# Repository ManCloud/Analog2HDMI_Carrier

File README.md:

# Analog2HDMI_Carrier
A breakout/carrier board for the Analog2HMDI adapter by Electron Shepherd LLC

Original project of the Circuit-Board.de / The-New-Retro (Discord) Community.

## Case
 https://www.printables.com/de/model/156339-analog2hdmi-case-for-manclouds-pcb
 
 ## Powered by:
 - jotheripper https://twitter.com/jotheripper_ (case)
 - FuNzeL https://twitter.com/Funzel86 (organization / ideas)
 - BambooShadow https://twitter.com/BambooShadow (prototyping)
 - derKevin https://twitter.com/kinoX_51 (ideas)
 - and the ones i forgot to mention.

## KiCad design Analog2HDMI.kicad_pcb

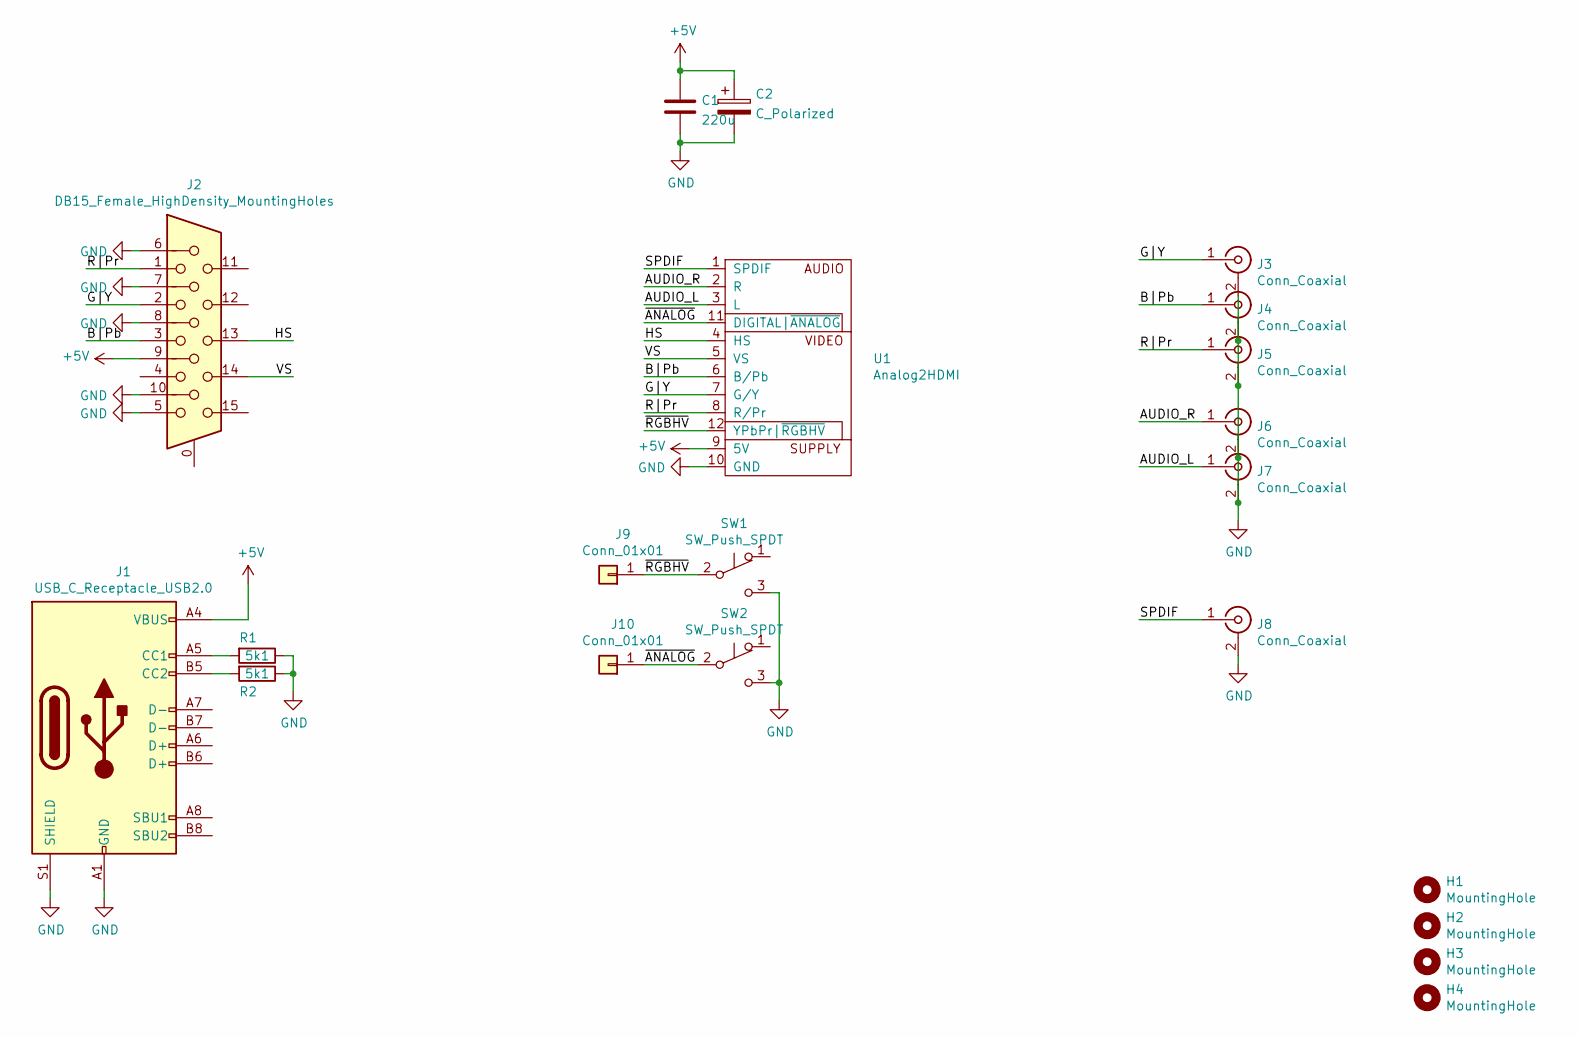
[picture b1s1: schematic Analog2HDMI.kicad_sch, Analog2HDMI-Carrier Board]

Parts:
C1: 220u; C_1206_3216Metric_Pad1.33x1.80mm_HandSolder
C2: C_Polarized; CP_Elec_6.3x7.7
H1, H2, H3, H4: MountingHole; MountingHole_2.1mm
J1: USB_C_Receptacle_USB2.0; USB_C_Receptacle_HRO_TYPE-C-31-M-12
J2: DB15_Female_HighDensity_MountingHoles; DSUB-15-HD_Female_Horizontal_P2.29x1.98mm_EdgePinOffset3.03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
J3, J4, J5, J6, J7, J8: Conn_Coaxial; AV-8.4-9
J9, J10: Conn_01x01; TestPoint_Pad_1.5x1.5mm
R1, R2: 5k1; R_1206_3216Metric
SW1, SW2: SW_Push_SPDT; SW_CuK_OS102011MA1QN1_SPDT_Angled
U1: Analog2HDMI

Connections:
+5V: C1.1, C2.1, J1.A4 (VBUS), J1.A9 (VBUS), J1.B4 (VBUS), J1.B9 (VBUS), J2.9, U1.9 (5V)
/AUDIO_L: J7.1 (In), U1.3 (L)
/AUDIO_R: J6.1 (In), U1.2 (R)
/B|Pb: J2.3, J4.1 (In), U1.6 (B/Pb)
/G|Y: J2.2, J3.1 (In), U1.7 (G/Y)
/HS: J2.13, U1.4 (HS)
/R|Pr: J2.1, J5.1 (In), U1.8 (R/Pr)
/SPDIF: J8.1 (In), U1.1 (SPDIF)
/VS: J2.14, U1.5 (VS)
/~ANALOG: J10.1, SW2.2 (B), U1.11 (DIGITAL|~ANALOG)
/~RGBHV: J9.1, SW1.2 (B), U1.12 (YPbPr|~RGBHV)
GND: C1.2, C2.2, J1.A1 (GND), J1.A12 (GND), J1.B1 (GND), J1.B12 (GND), J1.S1 (SHIELD), J2.5, J2.6, J2.7, J2.8, J2.10, J3.2 (Ext), J4.2 (Ext), J5.2 (Ext), J6.2 (Ext), J7.2 (Ext), J8.2 (Ext), R1.1, R2.1, SW1.3 (C), SW2.3 (C), U1.10 (GND)
unnamed: J1.A5 (CC1), R1.2
unnamed: J1.B5 (CC2), R2.2

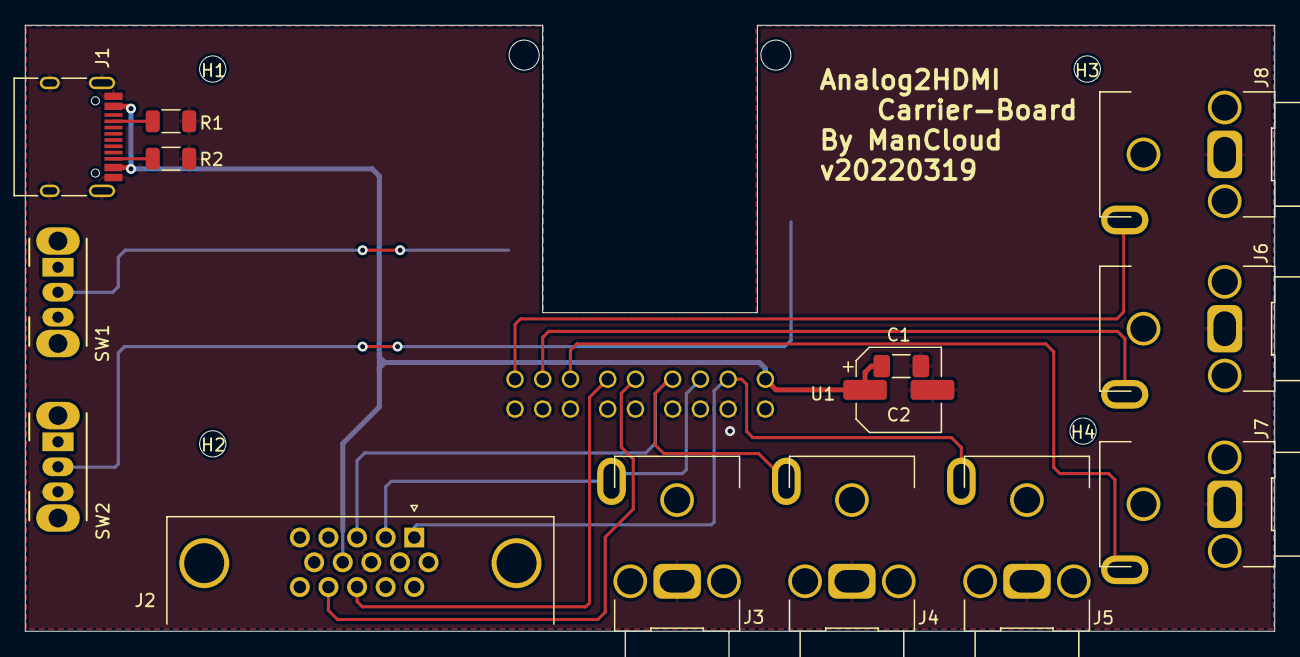
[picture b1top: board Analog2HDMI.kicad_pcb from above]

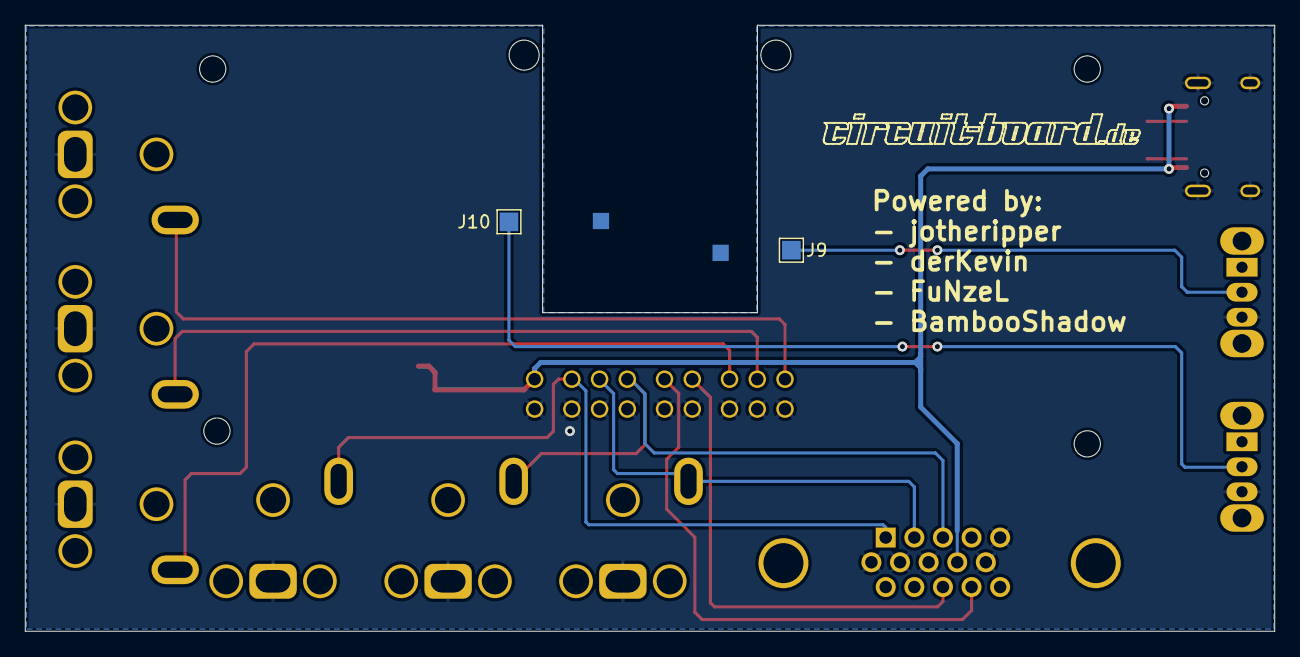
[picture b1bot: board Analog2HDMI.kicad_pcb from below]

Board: 2 copper layers, 100.0 x 48.5 mm, 21 parts (2 on the bottom side), 14 nets.

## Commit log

2021-12-13 v20211213
2022-09-12 updated to latest version
2022-09-12 removed unused files
2022-09-12 Update README.md
    corrected the baboo spelling
